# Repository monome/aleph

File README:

aleph.
:::::::::::::::::::::::::::::::::::::::::::::::::::::::::::::::::::::::::::
:::::::::::::::::::::::::::::::::::::::::::::::::::::::::::::::::::::::::::

:::::::::::::::::::::::::::::::::::::::::::::::::::::::::::::::::::::::::::
:::: quick start

is there an sdcard in it? there should be... then try:

- hold mode switch (square, upper right) while powering up to launch the bootloader [*]

- load an avr32 application from hex, in /hex folder on sdcard

- the unit should now reset and launch the chosen application. 

use usb cable and minicom/kermit to connect to aleph device port and get debug messages. 

currently using baudrate 500000 and a device spelled something like /dev/ttyACM0. [**] 

hints: 
sudo stty -F /dev/ttyACM0 500000
minicom -s
(serial port setup; then 'E' for bps; then 'a' until you see 500000; then 'f' OFF )

[*] for the "green sandwich" proto, mode switch is broken, bootloader toggle is SW4.

[**] for the "green sandwich" proto, the device is called /dev/ttyUSBx on linux, looks like FTDI,
and you may need to lower the baudrate.

:::::::::::::::::::::::::::::::::::::::::::::::::::::::::::::::::::::::::::
:::: device description

----------------------------
------ hardware:

aleph contains two processors:

1.	atmel AVR32 A0512.
	handles screen, encoders, panel switches, footswitches, USB, I2C, sdcard, and CV input.

2.	analog devices blackfin bf533.
	handles audio I/O, DSP processing, and CV output.

let's nickname these two processors the "controller" and the "dsp," respectively.

the controller is booted from internal flash memory.
it is connected to the dsp by an SPI bus (a fast, 3-wire serial protocol.)
to run a given audio program, the controller resets the dsp and sends a bootable binary image (.ldr) over the SPI bus.
with the dsp running, the same SPI bus carries parameter changes.

audio programs share a common format and protocol, much like an Audio Unit or VST plugin in software. 
each has a number of settable parameters, and metadata/descriptors for each.

the controller has a custom bootloader, which runs when a certain key combination is detected at powerup.
this bootloader is capable of flashing the internal memory with a new executable binary (.elf)

----------------------------------
---- software:

aleph will ship with a controller application called BEES. 
this is a relatively large and complex program designed to be as general-purpose as possible. 
it can arbitrarily and dynamically route and process control rate input, mangage multiple audio modules, 
store and recall configurations from sdcard.

but for some users and applications, it may make more sense to use or develop a single-purpose application 
(e.g. a loop pedal, monosynth, or some exotic experiment.) 
to encourage this kind of work, we will try to provide a relatively high-level API 
over the layers of software that communicate most directly with hardware on the avr32.
the app developer will presented with an array of handlers for handling UI or controller input, 
and an variety of functions for sending data to the dsp, to the screen, or to attached digital devices
(such as monomes, laptops, midi devices, and other alephs.)

the dsp side of the aleph presents another area of extendability. 
the different audio modules are similarly simple, 
building on both a hardware-specific firmware layer and a library of abstract fixed-point audio processors.

:::::::::::::::::::::::::::::::::::::::::::::::::::::::::::::::::::::::::::
:::: code directory structure

-----------------------
---- controller :

aleph/avr32_lib/src
	contains default low-level routines specific to the Aleph hardware.
	application authors can use these sources, or replace them with their own as desired.

aleph/avr32_lib/asf-x.x.x :
	a copy of the Atmel Software Framework.	
	this contains low-level drivers and utilies provided by Atmel, lightly modified by us.

aleph/apps : 
	contains a number of project directories which define actual functionality for the controller.
	each directory should contain app-specific sources and Makefile.

aleph/apps/bees:
	this is our main control routing/management application.

aleph/common : 
	routines that both the dsp and the controller need to agree on.
	this includes the SPI protocol and fixed-point math routines.

aleph/utils/avr32_boot  : 
	avr32 bootloader and hardware test program.

---------------------
---- dsp :

aleph/bfin_lib/src:	
	low-level sources for audio programs.
	these routines interact with the blackfin hardware directly, 
	and should be changed only with great care to avoid damaging the proces

aleph/modules :
	contains a number of project directories for specific audio modules.
	
aleph/dsp : 
	common audio functions implemented in 32-bit fixed-point,
	(envelopes, filters, buffers, oscillators, etc);
	these should be freely added to as needed by new modules.	
	currently there is no rigid class structure to these things, but we could impose one.

aleph/dsp/null : 
	a clunky little portaudio-based audio wrapper, 
	suitable for preliminary development of new audio modules.

development setup
----------------

clone git repository: 
git clone https://github.com/tehn/aleph.git

------------------
AVR32
-----

for mac:
https://github.com/droparea/avr32-toolchain

for linux:

get the toolchain and header files from atmel.com.

currently the page is here, (but it could move)
http://www.atmel.com/tools/ATMELAVRTOOLCHAINFORLINUX.aspx
you will need to sign up / login.

get the appopriate toolchain release for your architecture, and the latest headers,
now you have 2 files similar to:

avr32-gnu-toolchain-3.4.2.435-linux.any.x86.tar.gz
atmel-headers-6.1.3.1475.zip

GET 32 BIT.

extracting the toolchain archive gives you something like 
avr32-gnu-toolchain-linux_x86/

move/rename this directory however you like and make sure the binaries are in your $PATH

extracting the headers gives you
atmel-headers-6.1.3.1475

move or copy the headers subdirectories avr/ and avr32/ to the avr32/include/ subdirectory of the toolchain location.
no, i have no idea why atmel chose to do it this way!

here is an example of the whole process:

cd ~/Downloads

tar -xzf avr32-gnu-toolchain-3.4.2.435-linux.any.x86.tar.gz
unzip atmel-headers-6.1.3.1475.zip

mv avr32-gnu-toolchain-linux_x86 ~/avr32-gnu-toolchain
echo "PATH="\$PATH:~/avr32-gnu-toolchain/bin" >> ~/.bashrc
PATH=$PATH:~/avr32-gnu-toolchain/bin

cd atmel-headers-6.1.3.1475
cp avr/ ~/avr32-gnu-toolchain/avr32/include -R
cp avr32/ ~/avr32-gnu-toolchain/avr32/include/ -R

you should now be able to run 'make' from aleph/apps/bees and produce aleph-bees.hex. yeah!
let me know if there are problems: emb@catfact.net

--------------
BLACKFIN
-----

general instructions are here:
http://blackfin.uclinux.org/doku.php?id=toolchain:installing

we are only building standalone binaries (no uclinux), so only the bfin-elf-gcc toolchain is needed. 

get the most recent stable release for your architecture (2012-RC2 as of this writing), unpack it and add the binaries to your path. 

example: 
visit: http://sourceforge.net/projects/adi-toolchain/files/2012R2/2012R2-RC2/i386/blackfin-toolchain-elf-gcc-4.3-2012R2-RC2.i386.tar.bz2/download

:> cd ~/Downloads [or wherever]
:> su [probably]
:> mv blackfin-toolchain-elf-gcc-4.3-2012R2-RC2.i386.tar.bz2 /
:> cd /
:> tar -xjvf blackfin-toolchain-elf-gcc-4.3-2012R2-RC2.i386.tar.bz2
:> export PATH=$PATH:/opt/uClinux/bfin-elf/bin

the toolchain will be extracted to ./opt/uClinux by default.
of course you can use a different location if you like.
you probably also want to add the path to your .bashrc or whatever.

you should now be able to run 'make' from aleph/modules/lines or any other module.

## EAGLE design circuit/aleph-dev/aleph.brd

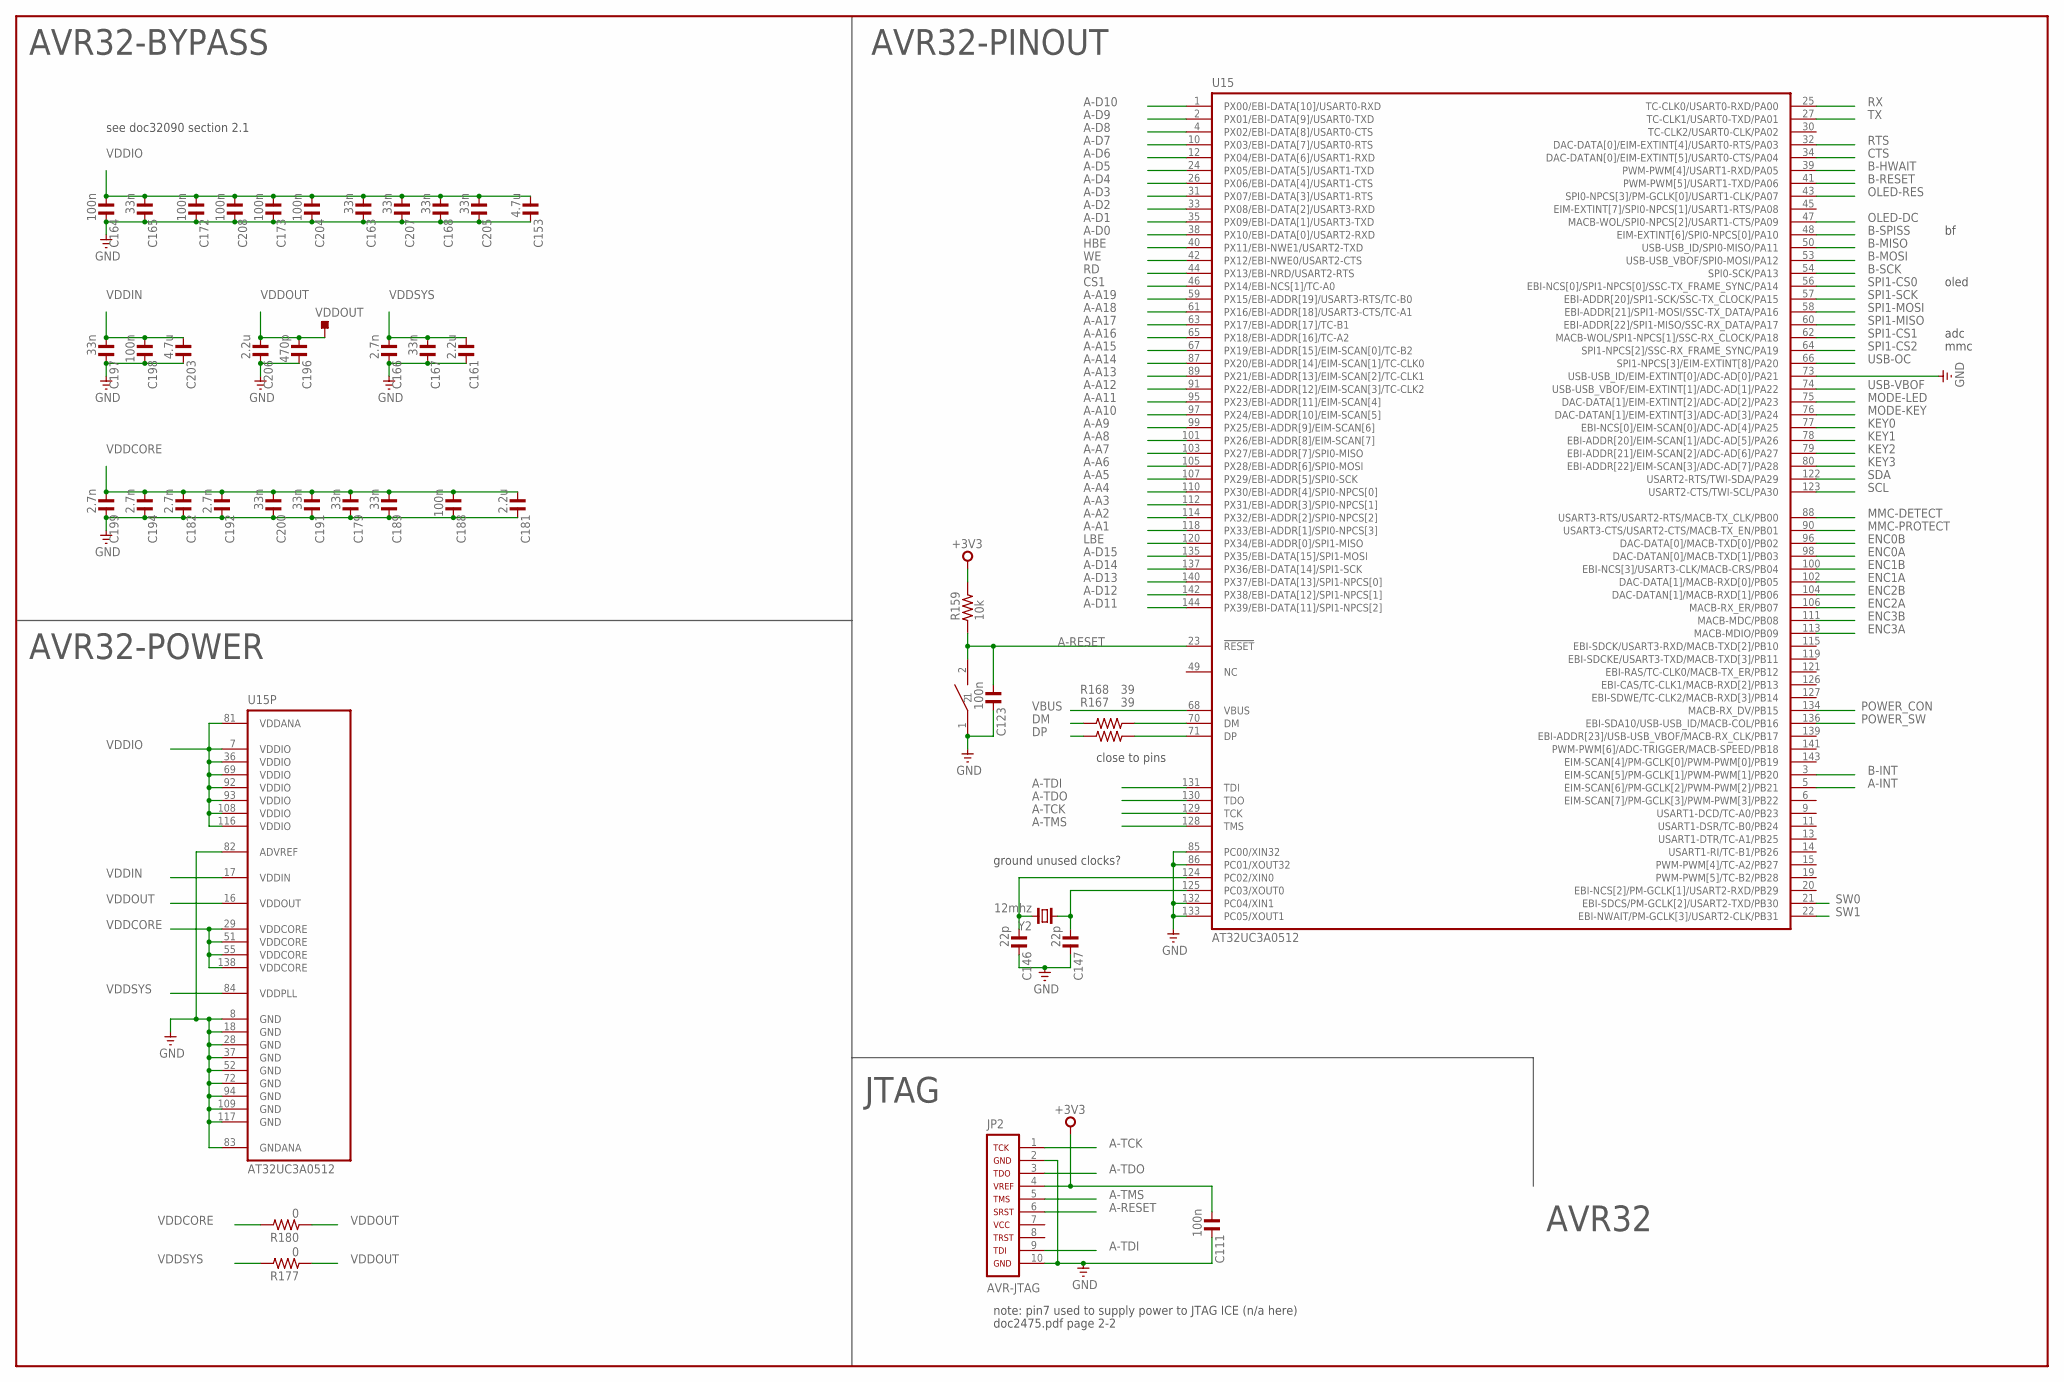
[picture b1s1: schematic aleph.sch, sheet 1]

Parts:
C111, C123, C164, C172, C173, C188, C198, C204, C208: 100n; C0603
C146, C147: 22p; C0603
C153, C203: 4.7u; C1206
C161, C181, C206: 2.2u; C1206
C163, C165, C167, C168, C179, C189, C191, C197, C200, C205, C207: 33n; C0603
C166, C182, C192, C194, C199: 2.7n; C0603
C196: 470p; C0603
JP2: AVR-JTAG; AVR-JTAG-10
R159: 10k; R0603
R167, R168: 39; R0603
R177, R180: 0; R0603
SW1: PANASONIC-EVQ
U15: AT32UC3A0512; LQFP144
VDDOUT: TPS-SMD-10R; SMD-10R
Y2: 12mhz; HC49UP

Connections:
+3V3: C111.1, JP2.4, R159.2; also elsewhere on the board
A-A1: U15.118 (PX33/EBI-ADDR[1]/SPI0-NPCS[3]); also elsewhere on the board
A-A2: U15.114 (PX32/EBI-ADDR[2]/SPI0-NPCS[2]); also elsewhere on the board
A-A3: U15.112 (PX31/EBI-ADDR[3]/SPI0-NPCS[1]); also elsewhere on the board
A-A4: U15.110 (PX30/EBI-ADDR[4]/SPI0-NPCS[0]); also elsewhere on the board
A-A5: U15.107 (PX29/EBI-ADDR[5]/SPI0-SCK); also elsewhere on the board
A-A6: U15.105 (PX28/EBI-ADDR[6]/SPI0-MOSI); also elsewhere on the board
A-A7: U15.103 (PX27/EBI-ADDR[7]/SPI0-MISO); also elsewhere on the board
A-A8: U15.101 (PX26/EBI-ADDR[8]/EIM-SCAN[7]); also elsewhere on the board
A-A9: U15.99 (PX25/EBI-ADDR[9]/EIM-SCAN[6]); also elsewhere on the board
A-A10: U15.97 (PX24/EBI-ADDR[10]/EIM-SCAN[5]); also elsewhere on the board
A-A11: U15.95 (PX23/EBI-ADDR[11]/EIM-SCAN[4]); also elsewhere on the board
A-A12: U15.91 (PX22/EBI-ADDR[12]/EIM-SCAN[3]/TC-CLK2); also elsewhere on the board
A-A13: U15.89 (PX21/EBI-ADDR[13]/EIM-SCAN[2]/TC-CLK1); also elsewhere on the board
A-A14: U15.87 (PX20/EBI-ADDR[14]/EIM-SCAN[1]/TC-CLK0); also elsewhere on the board
A-A15: U15.67 (PX19/EBI-ADDR[15]/EIM-SCAN[0]/TC-B2); also elsewhere on the board
A-A16: U15.65 (PX18/EBI-ADDR[16]/TC-A2); also elsewhere on the board
A-A17: U15.63 (PX17/EBI-ADDR[17]/TC-B1); also elsewhere on the board
A-A18: U15.61 (PX16/EBI-ADDR[18]/USART3-CTS/TC-A1); also elsewhere on the board
A-A19: U15.59 (PX15/EBI-ADDR[19]/USART3-RTS/TC-B0); also elsewhere on the board
A-D0: U15.38 (PX10/EBI-DATA[0]/USART2-RXD); also elsewhere on the board
A-D1: U15.35 (PX09/EBI-DATA[1]/USART3-TXD); also elsewhere on the board
A-D2: U15.33 (PX08/EBI-DATA[2]/USART3-RXD); also elsewhere on the board
A-D3: U15.31 (PX07/EBI-DATA[3]/USART1-RTS); also elsewhere on the board
A-D4: U15.26 (PX06/EBI-DATA[4]/USART1-CTS); also elsewhere on the board
A-D5: U15.24 (PX05/EBI-DATA[5]/USART1-TXD); also elsewhere on the board
A-D6: U15.12 (PX04/EBI-DATA[6]/USART1-RXD); also elsewhere on the board
A-D7: U15.10 (PX03/EBI-DATA[7]/USART0-RTS); also elsewhere on the board
A-D8: U15.4 (PX02/EBI-DATA[8]/USART0-CTS); also elsewhere on the board
A-D9: U15.2 (PX01/EBI-DATA[9]/USART0-TXD); also elsewhere on the board
A-D10: U15.1 (PX00/EBI-DATA[10]/USART0-RXD); also elsewhere on the board
A-D11: U15.144 (PX39/EBI-DATA[11]/SPI1-NPCS[2]); also elsewhere on the board
A-D12: U15.142 (PX38/EBI-DATA[12]/SPI1-NPCS[1]); also elsewhere on the board
A-D13: U15.140 (PX37/EBI-DATA[13]/SPI1-NPCS[0]); also elsewhere on the board
A-D14: U15.137 (PX36/EBI-DATA[14]/SPI1-SCK); also elsewhere on the board
A-D15: U15.135 (PX35/EBI-DATA[15]/SPI1-MOSI); also elsewhere on the board
A-INT: U15.5 (EIM-SCAN[6]/PM-GCLK[2]/PWM-PWM[2]/PB21); also elsewhere on the board
A-RESET: C123.1, JP2.6, R159.1, SW1.2, U15.23 (!RESET)
A-TCK: JP2.1, U15.129 (TCK)
A-TDI: JP2.9, U15.131 (TDI)
A-TDO: JP2.3, U15.130 (TDO)
A-TMS: JP2.5, U15.128 (TMS)
B-HWAIT: U15.39 (PWM-PWM[4]/USART1-RXD/PA05); also elsewhere on the board
B-INT: U15.3 (EIM-SCAN[5]/PM-GCLK[1]/PWM-PWM[1]/PB20); also elsewhere on the board
B-MISO: U15.50 (USB-USB_ID/SPI0-MISO/PA11); also elsewhere on the board
B-MOSI: U15.53 (USB-USB_VBOF/SPI0-MOSI/PA12); also elsewhere on the board
B-RESET: U15.41 (PWM-PWM[5]/USART1-TXD/PA06); also elsewhere on the board
B-SCK: U15.54 (SPI0-SCK/PA13); also elsewhere on the board
B-SPISS: U15.48 (EIM-EXTINT[6]/SPI0-NPCS[0]/PA10); also elsewhere on the board
CS1: U15.46 (PX14/EBI-NCS[1]/TC-A0); also elsewhere on the board
CTS: U15.34 (DAC-DATAN[0]/EIM-EXTINT[5]/USART0-CTS/P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); also elsewhere on the board
DM: R168.2; also elsewhere on the board
DP: R167.2; also elsewhere on the board
ENC0A: U15.98 (DAC-DATAN[0]/MACB-TXD[1]/PB03); also elsewhere on the board
ENC0B: U15.96 (DAC-DATA[0]/MACB-TXD[0]/PB02); also elsewhere on the board
ENC1A: U15.102 (DAC-DATA[1]/MACB-RXD[0]/PB05); also elsewhere on the board
ENC1B: U15.100 (EBI-NCS[3]/USART3-CLK/MACB-CRS/PB04); also elsewhere on the board
ENC2A: U15.106 (MACB-RX_ER/PB07); also elsewhere on the board
ENC2B: U15.104 (DAC-DATAN[1]/MACB-RXD[1]/PB06); also elsewhere on the board
ENC3A: U15.113 (MACB-MDIO/PB09); also elsewhere on the board
ENC3B: U15.111 (MACB-MDC/PB08); also elsewhere on the board
GND: C111.2, C123.2, C146.2, C147.2, C153.2, C161.2, C163.2, C164.2, C165.2, C166.2, C167.2, C168.2, C172.2, C173.2, C179.2, C181.2, C182.2, C188.2, C189.2, C191.2, C192.2, C194.2, C196.2, C197.2, C198.2, C199.2, C200.2, C203.2, C204.2, C205.2, C206.2, C207.2, C208.2, JP2.2, JP2.10, SW1.1, U15.8 (GND), U15.18 (GND), U15.28 (GND), U15.37 (GND), U15.52 (GND), U15.72 (GND), U15.73 (USB-USB_ID/EIM-EXTINT[0]/ADC-AD[0]/PA21), U15.82 (ADVREF), U15.83 (GNDANA), U15.85 (PC00/XIN32), U15.86 (PC01/XOUT32), U15.94 (GND), U15.109 (GND), U15.117 (GND), U15.132 (PC04/XIN1), U15.133 (PC05/XOUT1); also elsewhere on the board
HBE: U15.40 (PX11/EBI-NWE1/USART2-TXD); also elsewhere on the board
KEY0: U15.77 (EBI-NCS[0]/EIM-SCAN[0]/ADC-AD[4]/PA25); also elsewhere on the board
KEY1: U15.78 (EBI-ADDR[20]/EIM-SCAN[1]/ADC-AD[5]/PA26); also elsewhere on the board
KEY2: U15.79 (EBI-ADDR[21]/EIM-SCAN[2]/ADC-AD[6]/PA27); also elsewhere on the board
KEY3: U15.80 (EBI-ADDR[22]/EIM-SCAN[3]/ADC-AD[7]/PA28); also elsewhere on the board
LBE: U15.120 (PX34/EBI-ADDR[0]/SPI1-MISO); also elsewhere on the board
MMC-DETECT: U15.88 (USART3-RTS/USART2-RTS/MACB-TX_CLK/PB00); also elsewhere on the board
MMC-PROTECT: U15.90 (USART3-CTS/USART2-CTS/MACB-TX_EN/PB01); also elsewhere on the board
MODE-KEY: U15.76 (DAC-DATAN[1]/EIM-EXTINT[3]/ADC-AD[3]/PA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); also elsewhere on the board
MODE-LED: U15.75 (DAC-DATA[1]/EIM-EXTINT[2]/ADC-AD[2]/PA23); also elsewhere on the board
unnamed: C146.1, U15.124 (PC02/XIN0), Y2.2
unnamed: C147.1, U15.125 (PC03/XOUT0), Y2.1
unnamed: R168.1, U15.70 (DM)
unnamed: R167.1, U15.71 (DP)
OLED-DC: U15.47 (MACB-WOL/SPI0-NPCS[2]/USART1-CTS/PA09); also elsewhere on the board
OLED-RES: U15.43 (SPI0-NPCS[3]/PM-GCLK[0]/USART1-CLK/PA07); also elsewhere on the board
POWER_CON: U15.134 (MACB-RX_DV/PB15); also elsewhere on the board
POWER_SW: U15.136 (EBI-SDA10/USB-USB_ID/MACB-COL/PB16); also elsewhere on the board
RD: U15.44 (PX13/EBI-NRD/USART2-RTS); also elsewhere on the board
RTS: U15.32 (DAC-DATA[0]/EIM-EXTINT[4]/USART0-RTS/PA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); also elsewhere on the board
RX: U15.25 (TC-CLK0/USART0-RXD/PA00); also elsewhere on the board
SCL: U15.123 (USART2-CTS/TWI-SCL/PA30); also elsewhere on the board
SDA: U15.122 (USART2-RTS/TWI-SDA/PA29); also elsewhere on the board
SPI1-CS0: U15.56 (EBI-NCS[0]/SPI1-NPCS[0]/SSC-TX_FRAME_SY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); also elsewhere on the board
SPI1-CS1: U15.62 (MACB-WOL/SPI1-NPCS[1]/SSC-RX_CLOCK/PA18); also elsewhere on the board
SPI1-CS2: U15.64 (SPI1-NPCS[2]/SSC-RX_FRAME_SYNC/PA19); also elsewhere on the board
SPI1-MISO: U15.60 (EBI-ADDR[22]/SPI1-MISO/SSC-RX_DATA/PA17); also elsewhere on the board
SPI1-MOSI: U15.58 (EBI-ADDR[21]/SPI1-MOSI/SSC-TX_DATA/PA16); also elsewhere on the board
SPI1-SCK: U15.57 (EBI-ADDR[20]/SPI1-SCK/SSC-TX_CLOCK/PA15); also elsewhere on the board
SW0: U15.21 (EBI-SDCS/PM-GCLK[2]/USART2-TXD/PB30); also elsewhere on the board
SW1: U15.22 (EBI-NWAIT/PM-GCLK[3]/USART2-CLK/PB31); also elsewhere on the board
TX: U15.27 (TC-CLK1/USART0-TXD/PA01); also elsewhere on the board
USB-OC: U15.66 (SPI1-NPCS[3]/EIM-EXTINT[8]/PA20); also elsewhere on the board
USB-VBOF: U15.74 (USB-USB_VBOF/EIM-EXTINT[1]/ADC-AD[1]/PA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); also elsewhere on the board
VBUS: U15.68 (VBUS); also elsewhere on the board
VDDCORE: C179.1, C181.1, C182.1, C188.1, C189.1, C191.1, C192.1, C194.1, C199.1, C200.1, R180.2, U15.29 (VDDCORE), U15.51 (VDDCORE), U15.55 (VDDCORE), U15.138 (VDDCORE)
VDDIN: C197.1, C198.1, C203.1, U15.17 (VDDIN); also elsewhere on the board
VDDIO: C153.1, C163.1, C164.1, C165.1, C168.1, C172.1, C173.1, C204.1, C205.1, C207.1, C208.1, U15.7 (VDDIO), U15.36 (VDDIO), U15.69 (VDDIO), U15.81 (VDDANA), U15.92 (VDDIO), U15.93 (VDDIO), U15.108 (VDDIO), U15.116 (VDDIO); also elsewhere on the board
VDDOUT: C196.1, C206.1, R177.1, R180.1, U15.16 (VDDOUT), VDDOUT.TP
VDDSYS: C161.1, C166.1, C167.1, R177.2, U15.84 (VDDPLL)
WE: U15.42 (PX12/EBI-NWE0/USART2-CTS); also elsewhere on the board

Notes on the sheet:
note: pin7 used to supply power to JTAG ICE (n/a here)
doc2475.pdf page 2-2
ground unused clocks?
close to pins
see doc32090 section 2.1
mmc
adc
JTAG
AVR32-POWER
AVR32-BYPASS
AVR32-PINOUT
oled
AVR32

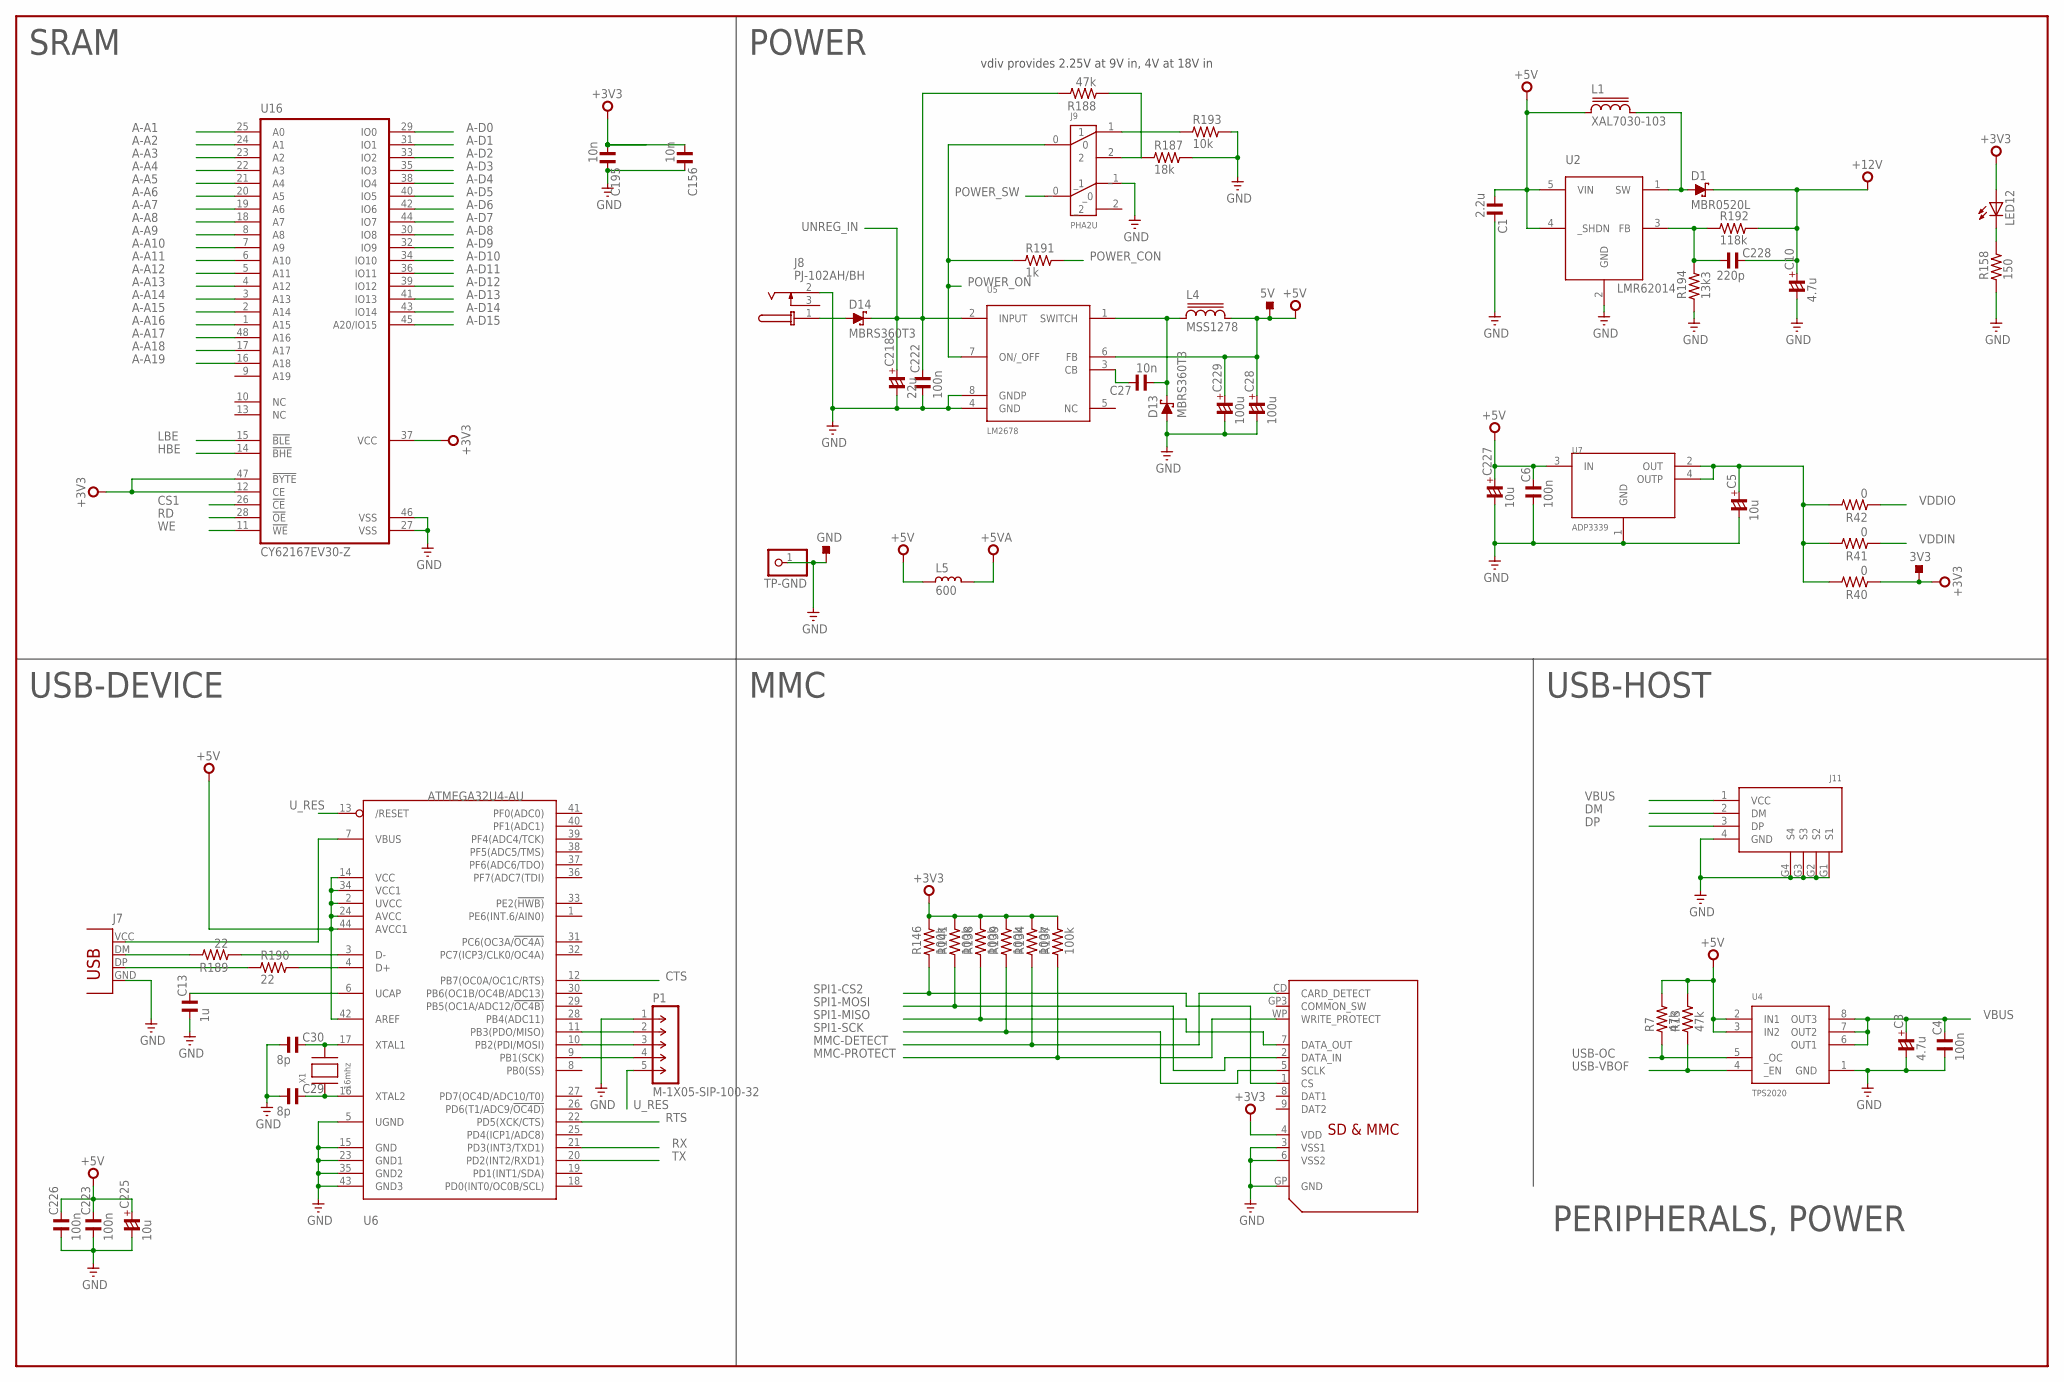
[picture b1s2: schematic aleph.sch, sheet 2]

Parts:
3V3, 5V: TPS-SMD-15R; SMD-15R
C1: 2.2u; C1206
C3, C10: 4.7u; C1206/T
C4, C223, C226: 100n; C0603
C5, C225, C227: 10u; C1206/T
C6, C222: 100n; C1206
C13: 1u; C0603
C27, C156, C195: 10n; C0603
C28, C229: 100u; C7343-43
C29, C30: 8p; C0603
C218: 22u; C6032-28/T
C228: 220p; C0603
D1: MBR0520L; SOD123
D13, D14: MBRS360T3; SMC
GND: TPS-SMD-20R; SMD-20R
J7: USB_TYPE_B; USB_B
J8: PJ-102AH/BH; PJ-102XH
J9: PHA2U
J11: USBA-VERT
L1: XAL7030-103
L4: MSS1278
L5: 600; L0603
LED12: LEDCHIPLED_0805; CHIPLED_0805
P1: M-1X05-SIP-100-32; SIP-100-05-32
R7, R13, R188: 47k; R0603
R40, R41, R42: 0; R0603
R134, R137, R138, R139, R141, R146: 100k; R0603
R158: 150; R0603
R187: 18k; R0603
R189, R190: 22; R0603
R191: 1k; R0603
R192: 118k; R0603
R193: 10k; R0603
R194: 13k3; R0603
S1: SDMMC06132; 06132
TP-GND: PINHD-1X1; 1X01
U2: LMR62014; SOT23-5
U4: TPS2020; SO08
U5: LM2678; TO263-7
U6: ATMEGA32U4-AU; TQFP44
U7: ADP3339; SOT223
U16: CY62167EV30-Z; TSOP48
X1: 16mhz; NX5032

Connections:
+3V3: 3V3.TP, C156.1, C195.1, LED12.A, R40.1, R134.2, R137.2, R138.2, R139.2, R141.2, R146.2, S1.4 (VDD), U16.12 (CE), U16.37 (VCC), U16.47 (!BYTE!); also elsewhere on the board
+5V: 5V.TP, C1.1, C6.2, C28.+, C223.2, C225.+, C226.2, C227.+, C229.+, L1.P$1 (1), L4.2, L5.2, R7.2, R13.2, U2.4 (_SHDN), U2.5 (VIN), U4.2 (IN1), U4.3 (IN2), U5.6 (FB), U6.2 (UVCC), U6.14 (VCC), U6.24 (AVCC), U6.34 (VCC1), U6.42 (AREF), U6.44 (AVCC1), U7.3 (IN); also elsewhere on the board
+5VA: L5.1; also elsewhere on the board
+12V: C10.+, C228.2, D1.C, R192.2; also elsewhere on the board
A-A1: U16.25 (A0); also elsewhere on the board
A-A2: U16.24 (A1); also elsewhere on the board
A-A3: U16.23 (A2); also elsewhere on the board
A-A4: U16.22 (A3); also elsewhere on the board
A-A5: U16.21 (A4); also elsewhere on the board
A-A6: U16.20 (A5); also elsewhere on the board
A-A7: U16.19 (A6); also elsewhere on the board
A-A8: U16.18 (A7); also elsewhere on the board
A-A9: U16.8 (A8); also elsewhere on the board
A-A10: U16.7 (A9); also elsewhere on the board
A-A11: U16.6 (A10); also elsewhere on the board
A-A12: U16.5 (A11); also elsewhere on the board
A-A13: U16.4 (A12); also elsewhere on the board
A-A14: U16.3 (A13); also elsewhere on the board
A-A15: U16.2 (A14); also elsewhere on the board
A-A16: U16.1 (A15); also elsewhere on the board
A-A17: U16.48 (A16); also elsewhere on the board
A-A18: U16.17 (A17); also elsewhere on the board
A-A19: U16.16 (A18); also elsewhere on the board
A-D0: U16.29 (IO0); also elsewhere on the board
A-D1: U16.31 (IO1); also elsewhere on the board
A-D2: U16.33 (IO2); also elsewhere on the board
A-D3: U16.35 (IO3); also elsewhere on the board
A-D4: U16.38 (IO4); also elsewhere on the board
A-D5: U16.40 (IO5); also elsewhere on the board
A-D6: U16.42 (IO6); also elsewhere on the board
A-D7: U16.44 (IO7); also elsewhere on the board
A-D8: U16.30 (IO8); also elsewhere on the board
A-D9: U16.32 (IO9); also elsewhere on the board
A-D10: U16.34 (IO10); also elsewhere on the board
A-D11: U16.36 (IO11); also elsewhere on the board
A-D12: U16.39 (IO12); also elsewhere on the board
A-D13: U16.41 (IO13); also elsewhere on the board
A-D14: U16.43 (IO14); also elsewhere on the board
A-D15: U16.45 (A20/IO15); also elsewhere on the board
CS1: U16.26 (!CE!); also elsewhere on the board
CTS: U6.12 (PB7(OC0A/OC1C/RTS)); also elsewhere on the board
DM: J11.2 (DM); also elsewhere on the board
DP: J11.3 (DP); also elsewhere on the board
GND: C1.2, C3.-, C4.1, C5.-, C6.1, C10.-, C13.1, C28.-, C29.1, C30.1, C156.2, C195.2, C218.-, C222.1, C223.1, C225.-, C226.1, C227.-, C229.-, D13.A, GND.TP, J7.GND, J8.2 (S), J9._1, J11.4 (GND), J11.G1 (S1), J11.G2 (S2), J11.G3 (S3), J11.G4 (S4), P1.1, R158.1, R187.2, R193.2, R194.1, S1.3 (VSS1), S1.6 (VSS2), S1.GP (GND), TP-GND.1, U2.2 (GND), U4.1 (GND), U5.4 (GND), U5.8 (GNDP), U6.5 (UGND), U6.15 (GND), U6.23 (GND1), U6.35 (GND2), U6.43 (GND3), U7.1 (GND), U16.27 (VSS), U16.46 (VSS); also elsewhere on the board
HBE: U16.14 (!BHE!); also elsewhere on the board
LBE: U16.15 (!BLE!); also elsewhere on the board
MMC-DETECT: R134.1, S1.CD (CARD_DETECT); also elsewhere on the board
MMC-PROTECT: R137.1, S1.WP (WRITE_PROTECT); also elsewhere on the board
unnamed: D14.A, J8.1 (T)
unnamed: J7.DM (USBDM), R189.2
unnamed: C27.1, D13.C, L4.1, U5.1 (SWITCH)
unnamed: C27.2, U5.3 (CB)
unnamed: J7.DP (USBDP), R190.1
unnamed: R190.2, U6.4 (D+)
unnamed: LED12.C, R158.2
unnamed: R189.1, U6.3 (D-)
unnamed: C5.+, R40.2, R41.2, R42.2, U7.2 (OUT), U7.4 (OUTP)
unnamed: J9.1, R193.1
unnamed: J9.2, R187.1, R188.1
unnamed: C29.2, U6.16 (XTAL2), X1.P$1
unnamed: C30.2, U6.17 (XTAL1), X1.P$2
unnamed: D1.A, L1.P$2 (2), U2.1 (SW)
unnamed: C228.1, R192.1, R194.2, U2.3 (FB)
unnamed: C13.2, U6.6 (UCAP)
unnamed: J7.VCC, U6.7 (VBUS)
POWER_CON: R191.2; also elsewhere on the board
POWER_ON: J9.0, R191.1, U5.7 (ON/_OFF)
POWER_SW: J9._0; also elsewhere on the board
RD: U16.28 (!OE!); also elsewhere on the board
RTS: U6.22 (PD5(XCK/CTS)); also elsewhere on the board
RX: U6.21 (PD3(INT3/TXD1)); also elsewhere on the board
SPI1-CS2: R146.1, S1.1 (CS); also elsewhere on the board
SPI1-MISO: R138.1, S1.7 (DATA_OUT); also elsewhere on the board
SPI1-MOSI: R141.1, S1.2 (DATA_IN); also elsewhere on the board
SPI1-SCK: R139.1, S1.5 (SCLK); also elsewhere on the board
TX: U6.20 (PD2(INT2/RXD1)); also elsewhere on the board
U-MISO: P1.2, U6.11 (PB3(PDO/MISO))
U-MOSI: P1.3, U6.10 (PB2(PDI/MOSI))
U-SCK: P1.4, U6.9 (PB1(SCK))
UNREG_IN: C218.+, C222.2, D14.C, R188.2, U5.2 (INPUT)
USB-OC: R7.1, U4.5 (_OC); also elsewhere on the board
USB-VBOF: R13.1, U4.4 (_EN); also elsewhere on the board
U_RES: P1.5, U6.13 (/RESET)
VBUS: C3.+, C4.2, J11.1 (VCC), U4.6 (OUT1), U4.7 (OUT2), U4.8 (OUT3); also elsewhere on the board
VDDIN: R41.1; also elsewhere on the board
VDDIO: R42.1; also elsewhere on the board
WE: U16.11 (!WE!); also elsewhere on the board

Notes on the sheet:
SRAM
MMC
USB-HOST
USB-DEVICE
vdiv provides 2.25V at 9V in, 4V at 18V in
POWER
PERIPHERALS, POWER

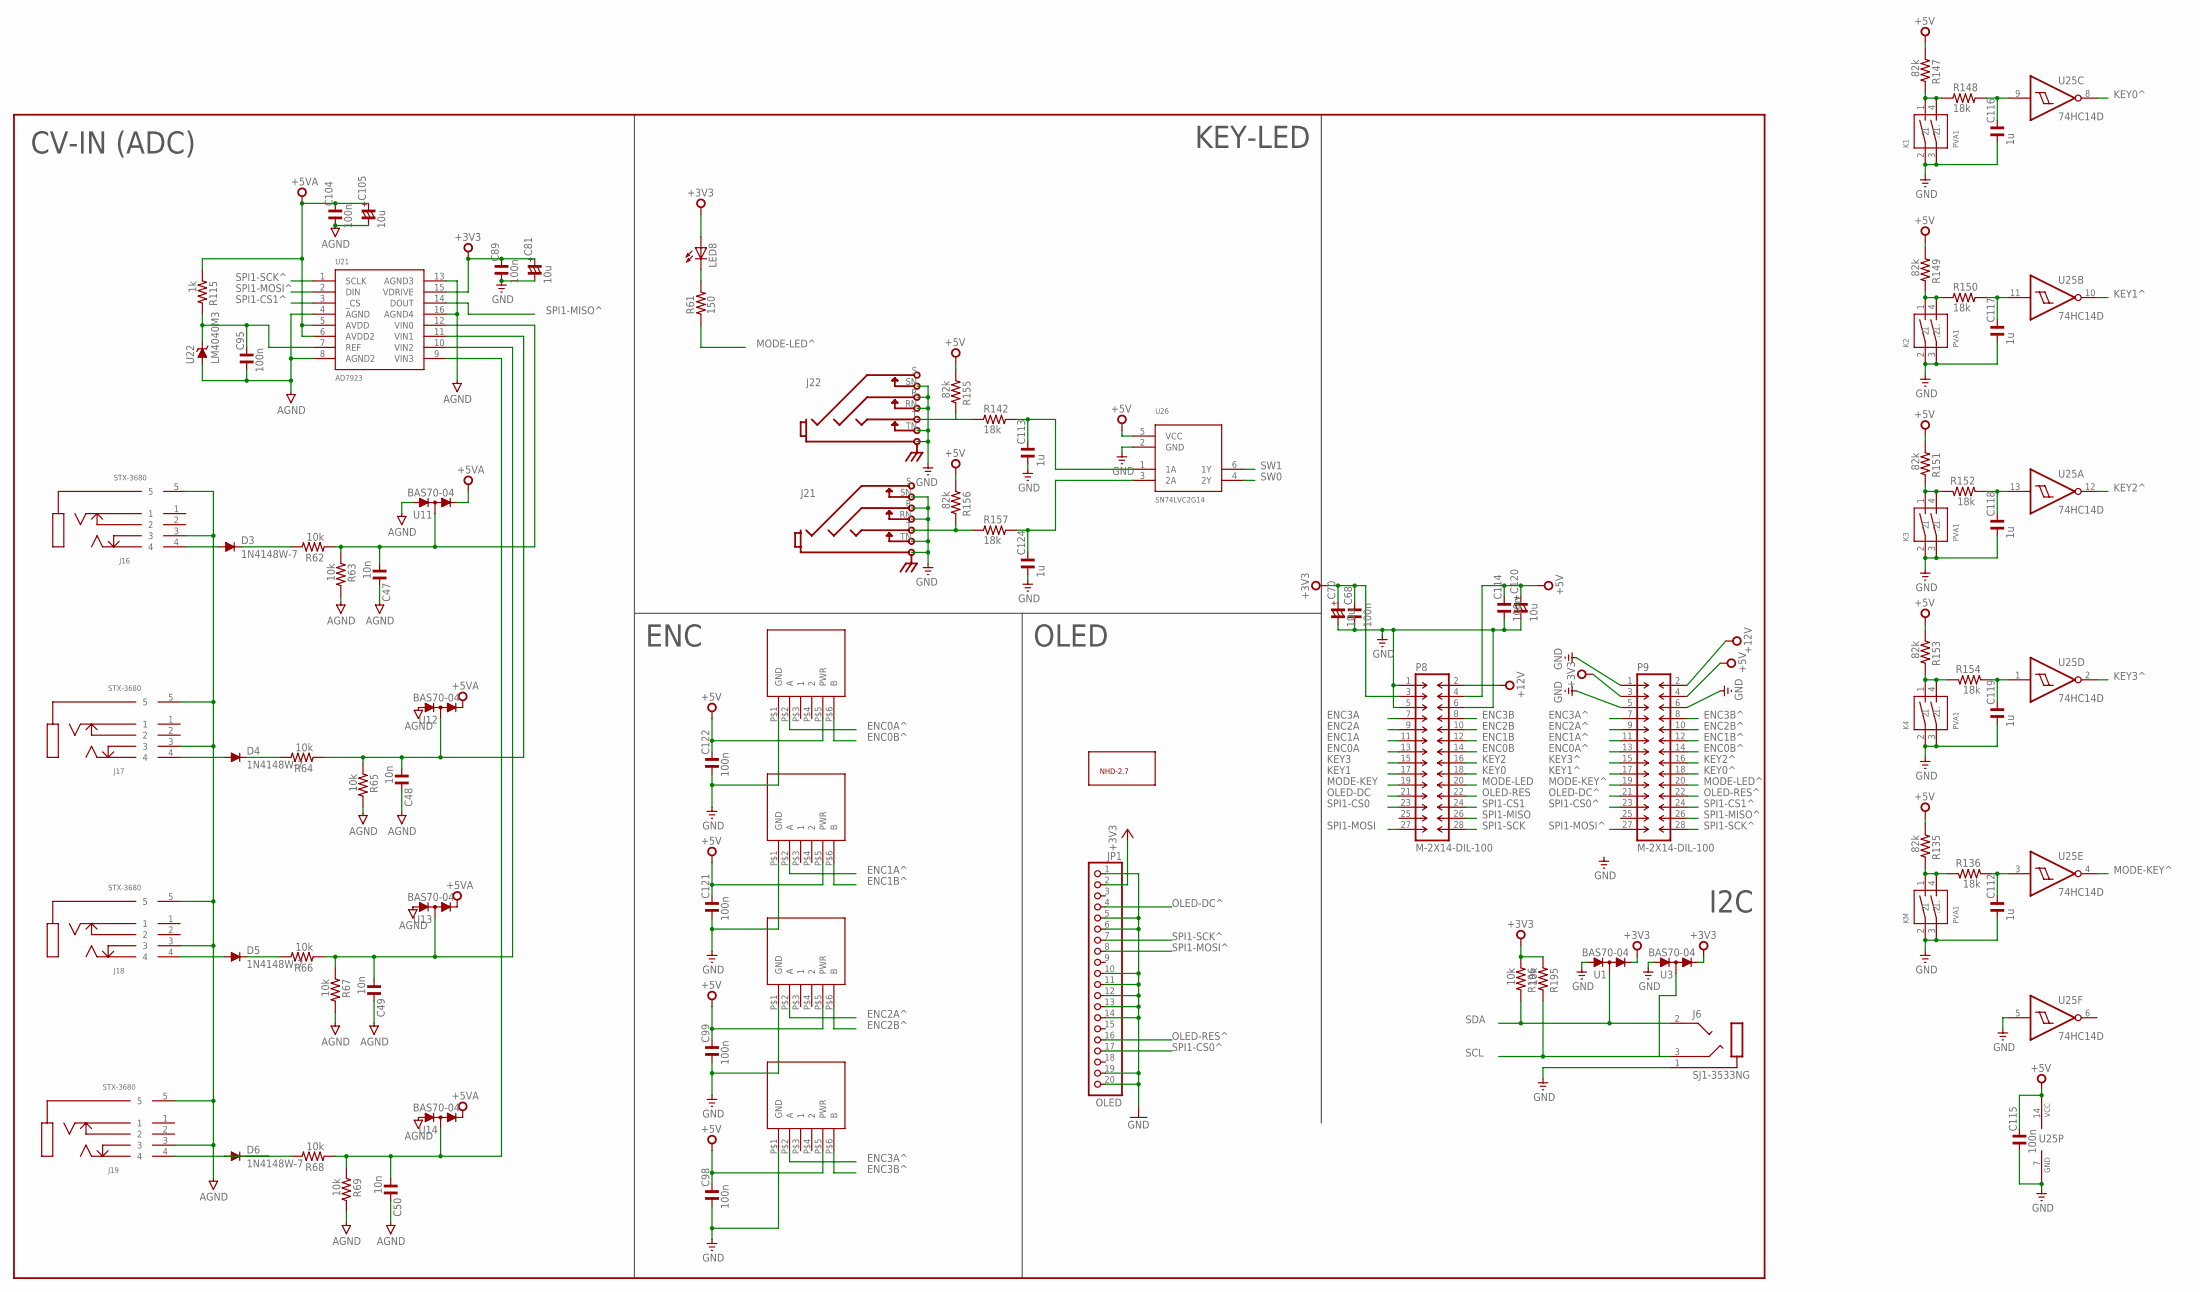
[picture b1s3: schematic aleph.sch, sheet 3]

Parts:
C47, C48, C49, C50: 10n; C0603
C68, C89, C95, C98, C99, C104, C114, C115, C121, C122: 100n; C0603
C70, C81, C105, C120: 10u; C1206/T
C112, C113, C116, C117, C118, C119, C124: 1u; C0603
D3, D4, D5, D6: 1N4148W-7; SOD123
E1, E2, E3, E4: BOURNS-EM14
J6: SJ1-3533NG
J16, J17, J18, J19: STX-3680
J21, J22: STEREOSW3GND; NEUTRIK-NRJ6HF-1
JP1: OLED; 1X20
K1, K2, K3, K4: PVA1
KM: PVA1
LED8: LEDCHIPLED_0805; CHIPLED_0805
P8, P9: M-2X14-DIL-100; DIL-100-2X14
R61: 150; R0603
R62, R63, R64, R65, R66, R67, R68, R69, R195, R196: 10k; R0603
R115: 1k; R0603
R135, R147, R149, R151, R153, R155, R156: 82k; R0603
R136, R142, R148, R150, R152, R154, R157: 18k; R0603
REF-OLED: NHD-2.7
U1, U3, U11, U12, U13, U14: BAS70-04; SOT23
U21: AD7923; TSSOP16
U22: LM4040M3; SOT23
U25: 74HC14D; SO14
U26: SN74LVC2G14; SOT23-6

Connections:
+3V3: C68.2, C70.+, C81.+, C89.2, JP1.2, LED8.A, P8.3, P9.3, R195.1, R196.1, U1.2 (C), U3.2 (C), U21.15 (VDRIVE); also elsewhere on the board
+5V: C98.2, C99.2, C114.2, C115.2, C120.+, C121.2, C122.2, E1.P$5 (PWR), E2.P$5 (PWR), E3.P$5 (PWR), E4.P$5 (PWR), P8.4, P9.4, R135.1, R147.1, R149.1, R151.1, R153.1, R155.1, R156.1, U25.14 (VCC), U26.5 (VCC); also elsewhere on the board
+5VA: C104.2, C105.+, R115.1, U11.2 (C), U12.2 (C), U13.2 (C), U14.2 (C), U21.5 (AVDD), U21.6 (AVDD2); also elsewhere on the board
+12V: P8.2, P9.2; also elsewhere on the board
AGND: C47.2, C48.2, C49.2, C50.2, C95.1, C104.1, C105.-, J16.3, J16.5, J17.3, J17.5, J18.3, J18.5, J19.3, J19.5, R63.2, R65.2, R67.2, R69.2, U11.1 (A), U12.1 (A), U13.1 (A), U14.1 (A), U21.4 (AGND), U21.8 (AGND2), U21.13 (AGND3), U21.16 (AGND4), U22.2 (A); also elsewhere on the board
ENC0A: P8.13; also elsewhere on the board
ENC0A^: E1.P$2 (A), P9.13
ENC0B: P8.14; also elsewhere on the board
ENC0B^: E1.P$6 (B), P9.14
ENC1A: P8.11; also elsewhere on the board
ENC1A^: E2.P$2 (A), P9.11
ENC1B: P8.12; also elsewhere on the board
ENC1B^: E2.P$6 (B), P9.12
ENC2A: P8.9; also elsewhere on the board
ENC2A^: E4.P$2 (A), P9.9
ENC2B: P8.10; also elsewhere on the board
ENC2B^: E4.P$6 (B), P9.10
ENC3A: P8.7; also elsewhere on the board
ENC3A^: E3.P$2 (A), P9.7
ENC3B: P8.8; also elsewhere on the board
ENC3B^: E3.P$6 (B), P9.8
GND: C68.1, C70.-, C81.-, C89.1, C98.1, C99.1, C112.1, C113.1, C114.1, C115.1, C116.1, C117.1, C118.1, C119.1, C120.-, C121.1, C122.1, C124.1, E1.P$1 (GND), E2.P$1 (GND), E3.P$1 (GND), E4.P$1 (GND), J6.1 (S), J21.R, J21.RN, J21.SN, J21.TN, J22.R, J22.RN, J22.SN, J22.TN, JP1.1, JP1.5, JP1.6, JP1.10, JP1.11, JP1.12, JP1.13, JP1.14, JP1.19, JP1.20, K1.2 (1), K1.3 (1.), K2.2 (1), K2.3 (1.), K3.2 (1), K3.3 (1.), K4.2 (1), K4.3 (1.), KM.2 (1), KM.3 (1.), P8.1, P8.5, P8.6, P9.1, P9.5, P9.6, U1.1 (A), U3.1 (A), U25.5 (I), U25.7 (GND), U26.2 (GND); also elsewhere on the board
KEY0: P8.18; also elsewhere on the board
KEY0^: P9.18, U25.8 (O)
KEY1: P8.17; also elsewhere on the board
KEY1^: P9.17, U25.10 (O)
KEY2: P8.16; also elsewhere on the board
KEY2^: P9.16, U25.12 (O)
KEY3: P8.15; also elsewhere on the board
KEY3^: P9.15, U25.2 (O)
MODE-KEY: P8.19; also elsewhere on the board
MODE-KEY^: P9.19, U25.4 (O)
MODE-LED: P8.20; also elsewhere on the board
MODE-LED^: P9.20, R61.1
unnamed: K1.1 (2), K1.4 (.2), R147.2, R148.1
unnamed: C116.2, R148.2, U25.9 (I)
unnamed: K2.1 (2), K2.4 (.2), R149.2, R150.1
unnamed: C117.2, R150.2, U25.11 (I)
unnamed: LED8.C, R61.2
unnamed: K3.1 (2), K3.4 (.2), R151.2, R152.2
unnamed: C118.2, R152.1, U25.13 (I)
unnamed: K4.1 (2), K4.4 (.2), R153.2, R154.2
unnamed: C119.2, R154.1, U25.1 (I)
unnamed: D3.A, J16.4
unnamed: D4.C, R64.2
unnamed: D3.C, R62.2
unnamed: D5.C, R66.2
unnamed: D4.A, J17.4
unnamed: KM.1 (2), KM.4 (.2), R135.2, R136.2
unnamed: D6.C, R68.2
unnamed: D5.A, J18.4
unnamed: C112.2, R136.1, U25.3 (I)
unnamed: D6.A, J19.4
unnamed: C124.2, R157.2, U26.3 (2A)
unnamed: C95.2, R115.2, U21.7 (REF), U22.1 (C)
unnamed: C48.1, R64.1, R65.1, U12.3 (AC), U21.11 (VIN1)
unnamed: C49.1, R66.1, R67.1, U13.3 (AC), U21.10 (VIN2)
unnamed: C50.1, R68.1, R69.1, U14.3 (AC), U21.9 (VIN3)
unnamed: C47.1, R62.1, R63.1, U11.3 (AC), U21.12 (VIN0)
unnamed: C113.2, R142.2, U26.1 (1A)
OLED-DC: P8.21; also elsewhere on the board
OLED-DC^: JP1.4, P9.21
OLED-RES: P8.22; also elsewhere on the board
OLED-RES^: JP1.16, P9.22
SCL: J6.3 (R), R195.2, U3.3 (AC); also elsewhere on the board
SDA: J6.2 (T), R196.2, U1.3 (AC); also elsewhere on the board
SPI1-CS0: P8.23; also elsewhere on the board
SPI1-CS0^: JP1.17, P9.23
SPI1-CS1: P8.24; also elsewhere on the board
SPI1-CS1^: P9.24, U21.3 (_CS)
SPI1-MISO: P8.26; also elsewhere on the board
SPI1-MISO^: P9.26, U21.14 (DOUT)
SPI1-MOSI: P8.27; also elsewhere on the board
SPI1-MOSI^: JP1.8, P9.27, U21.2 (DIN)
SPI1-SCK: P8.28; also elsewhere on the board
SPI1-SCK^: JP1.7, P9.28, U21.1 (SCLK)
SW0: U26.4 (2Y); also elsewhere on the board
SW0CON^: J22.T, R142.1, R155.2
SW1: U26.6 (1Y); also elsewhere on the board
SW1CON^: J21.T, R156.2, R157.1

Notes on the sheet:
I2C
OLED
KEY-LED
CV-IN (ADC)
ENC
